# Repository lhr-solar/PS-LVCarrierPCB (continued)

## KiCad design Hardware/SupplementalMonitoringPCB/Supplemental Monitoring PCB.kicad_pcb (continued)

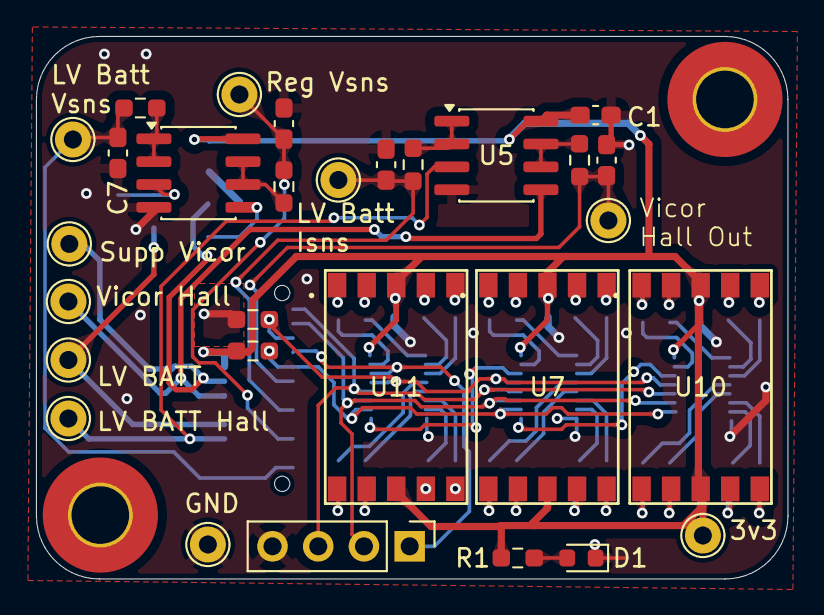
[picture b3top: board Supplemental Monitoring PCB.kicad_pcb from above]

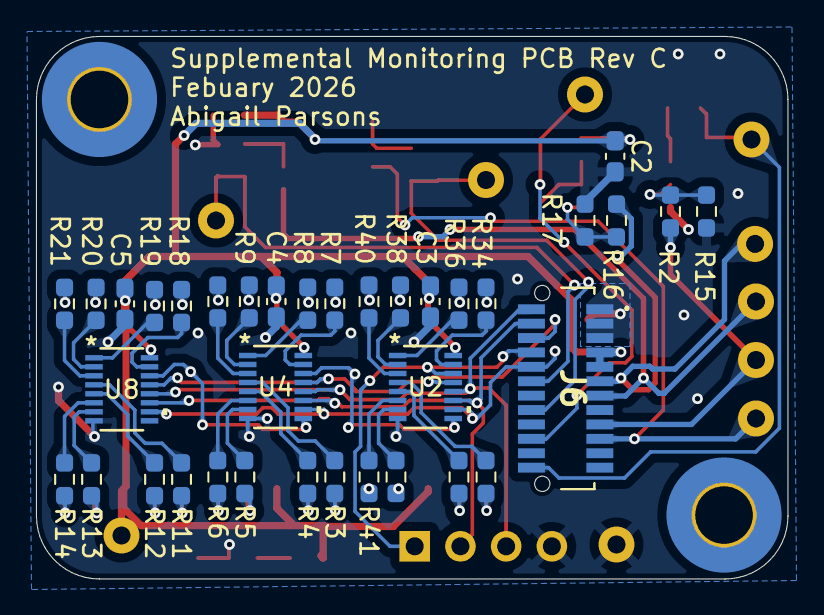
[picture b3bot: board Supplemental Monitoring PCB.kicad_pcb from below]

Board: 2 copper layers, 41.8 x 30.1 mm, 68 parts (36 on the bottom side), 72 nets.

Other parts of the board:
J1: Conn_01x04; PinHeader_1x04_P2.54mm_Vertical

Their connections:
/RCLK: J1.3; also elsewhere on the board
/SER: J1.1; also elsewhere on the board
/SRCLK: J1.2; also elsewhere on the board
GND: J1.4; also elsewhere on the board

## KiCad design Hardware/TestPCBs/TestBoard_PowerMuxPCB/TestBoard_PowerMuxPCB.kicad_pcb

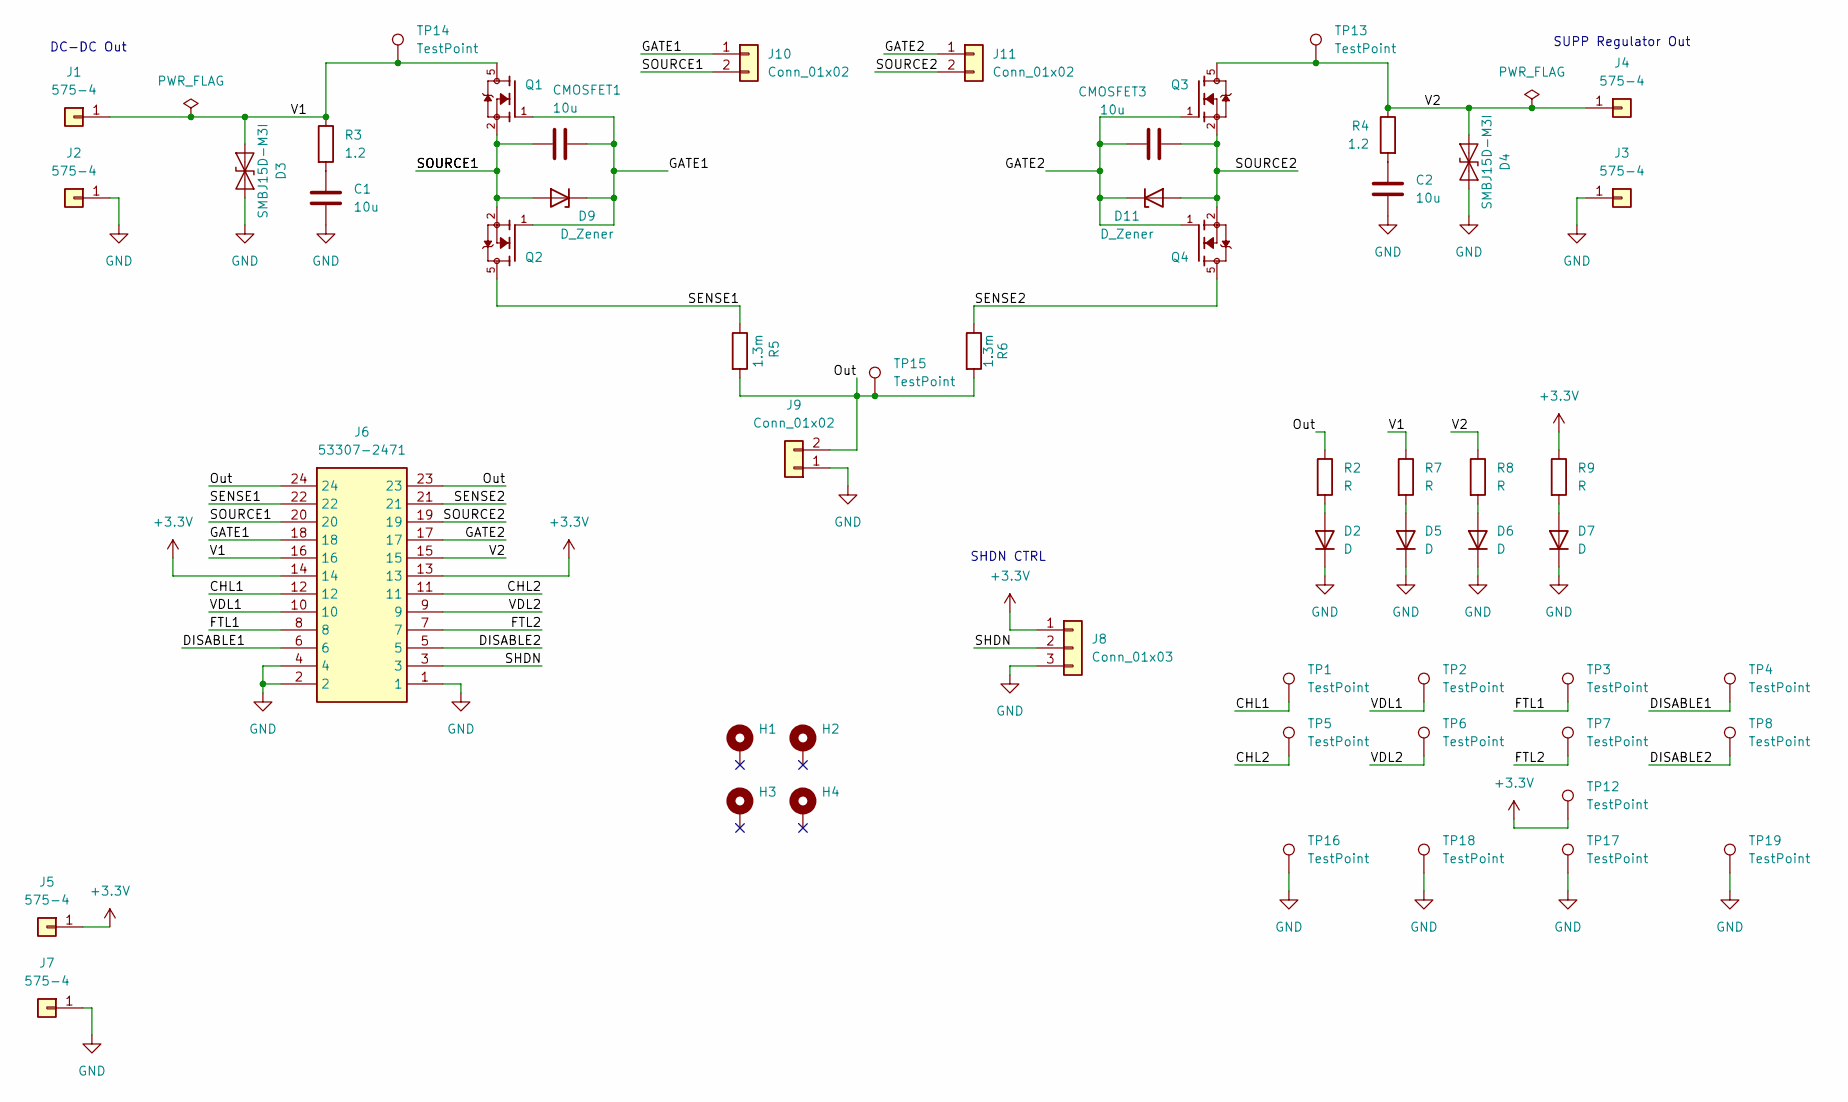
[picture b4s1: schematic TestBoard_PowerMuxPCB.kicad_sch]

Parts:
C1, C2: 10u; C_0805_2012Metric
CMOSFET1, CMOSFET3: 10u; C_0805_2012Metric
D2, D5, D6, D7: D; LED_0603_1608Metric
D3, D4: SMBJ15D-M3I; SMBJ15DM3; MFG PN SMBJ15D-M3I
D9, D11: D_Zener; D_SOD-523; MFG PN DDZ9703T-7
H1, H2, H3, H4: MountingHole_Pad; MountingHole_3.2mm_M3_Pad
J1, J2, J3, J4, J5, J7: 575-4; 5754
J6: 53307-2471; LVMux; Mouser Part Number 538-53307-2471
J8: Conn_01x03; PinHeader_1x03_P2.54mm_Vertical
J9: Conn_01x02; AMASS_XT30UPB-M_1x02_P5.0mm_Vertical
J10, J11: Conn_01x02; PinHeader_1x02_P2.54mm_Vertical
Q1, Q2, Q3, Q4: SQJQ140E-T1_GE3; PARTREV 05-Aug-2019
R2, R7, R8, R9: R; R_0603_1608Metric_Pad0.98x0.95mm_HandSolder
R3, R4: 1.2; R_0805_2012Metric; MFG PN CRCW06031R20FKEA
R5, R6: 1.3m; RESC6432X89N
TP1, TP2, TP3, TP4, TP5, TP6, TP7, TP8, TP12, TP13, TP14, TP15, TP16, TP17, TP18, TP19: TestPoint; TestPoint_Loop_D3.50mm_Drill1.4mm_Beaded

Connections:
+3.3V: J5.1, J6.13, J6.14, J8.1, R9.1, TP12.1
/CHL1: J6.12, TP1.1
/CHL2: J6.11, TP5.1
/DISABLE1: J6.6, TP4.1
/DISABLE2: J6.5, TP8.1
/FTL1: J6.8, TP3.1
/FTL2: J6.7, TP7.1
/GATE1: CMOSFET1.2, D9.1 (K), J6.18, J10.1, Q1.1, Q2.1
/GATE2: CMOSFET3.2, D11.1 (K), J6.17, J11.1, Q3.1, Q4.1
/Out: J6.23, J6.24, J9.2, R2.1, R5.2, R6.2, TP15.1
/SENSE1: J6.22, Q2.5, R5.1
/SENSE2: J6.21, Q4.5, R6.1
/SHDN: J6.3, J8.2
/SOURCE1: CMOSFET1.1, D9.2 (A), J6.20, J10.2, Q1.2, Q1.3, Q1.4, Q2.2, Q2.3, Q2.4
/SOURCE2: CMOSFET3.1, D11.2 (A), J6.19, J11.2, Q3.2, Q3.3, Q3.4, Q4.2, Q4.3, Q4.4
/V1: D3.1 (K), J1.1, J6.16, Q1.5, R3.1, R7.1, TP14.1
/V2: D4.1 (K), J4.1, J6.15, Q3.5, R4.1, R8.1, TP13.1
/VDL1: J6.10, TP2.1
/VDL2: J6.9, TP6.1
GND: C1.2, C2.2, D2.1 (K), D3.2 (A), D4.2 (A), D5.1 (K), D6.1 (K), D7.1 (K), J2.1, J3.1, J6.1, J6.2, J6.4, J7.1, J8.3, J9.1, TP16.1, TP17.1, TP18.1, TP19.1
unnamed: C1.1, R3.2
unnamed: C2.1, R4.2
unnamed: D2.2 (A), R2.2
unnamed: D5.2 (A), R7.2
unnamed: D6.2 (A), R8.2
unnamed: D7.2 (A), R9.2

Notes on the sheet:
SUPP Regulator Out
SHDN CTRL
DC-DC Out

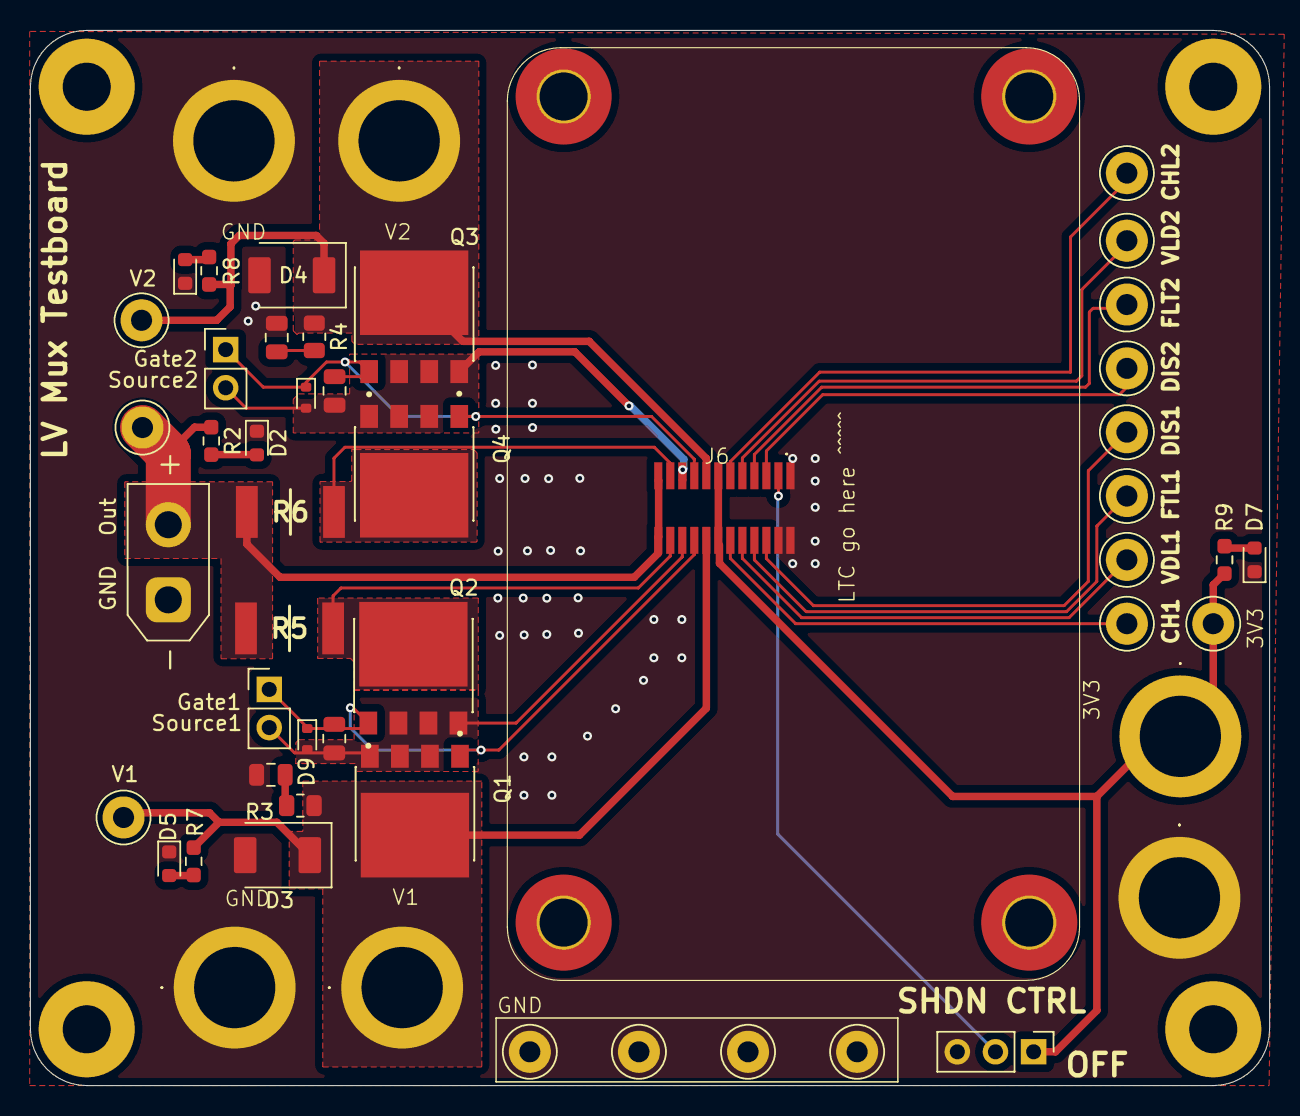
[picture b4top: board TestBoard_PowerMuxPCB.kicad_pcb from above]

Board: 2 copper layers, 82.5 x 70.2 mm, 55 parts (0 on the bottom side), 26 nets.

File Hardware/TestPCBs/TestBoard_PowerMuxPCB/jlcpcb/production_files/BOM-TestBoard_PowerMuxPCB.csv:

Comment,Designator,Footprint,LCSC,Quantity
53307-2471,J6,LVMux,,1
D,D2,LED_0603_1608Metric,,1
R,R8,R_0603_1608Metric_Pad0.98x0.95mm_HandSolder,,1
R,R7,R_0603_1608Metric_Pad0.98x0.95mm_HandSolder,,1
575-4,J5,5754,,1
SQJQ140E-T1_GE3,Q4,SQJQ140E-T1_GE3,,1
D,D5,LED_0603_1608Metric,,1
SQJQ140E-T1_GE3,Q3,SQJQ140E-T1_GE3,,1
1.3m,R5,RESC6432X89N,,1
575-4,J2,5754,,1
SMBJ15D-M3I,D4,SMBJ15DM3,,1
D,D7,LED_0603_1608Metric,,1
575-4,J7,5754,,1
D_Zener,D11,D_SOD-523,,1
SQJQ140E-T1_GE3,Q2,SQJQ140E-T1_GE3,,1
SQJQ140E-T1_GE3,Q1,SQJQ140E-T1_GE3,,1
575-4,J3,5754,,1
D,D6,LED_0603_1608Metric,,1
1.2,R3,R_0805_2012Metric,,1
1.2,R4,R_0805_2012Metric,,1
575-4,J1,5754,,1
575-4,J4,5754,,1
D_Zener,D9,D_SOD-523,,1
R,R2,R_0603_1608Metric_Pad0.98x0.95mm_HandSolder,,1
SMBJ15D-M3I,D3,SMBJ15DM3,,1
10u,C1,C_0805_2012Metric,,1
1.3m,R6,RESC6432X89N,,1
Conn_01x02,J9,AMASS_XT30UPB-M_1x02_P5.0mm_Vertical,,1
R,R9,R_0603_1608Metric_Pad0.98x0.95mm_HandSolder,,1
10u,C2,C_0805_2012Metric,,1
Conn_01x02,J11,PinHeader_1x02_P2.54mm_Vertical,,1
Conn_01x02,J10,PinHeader_1x02_P2.54mm_Vertical,,1

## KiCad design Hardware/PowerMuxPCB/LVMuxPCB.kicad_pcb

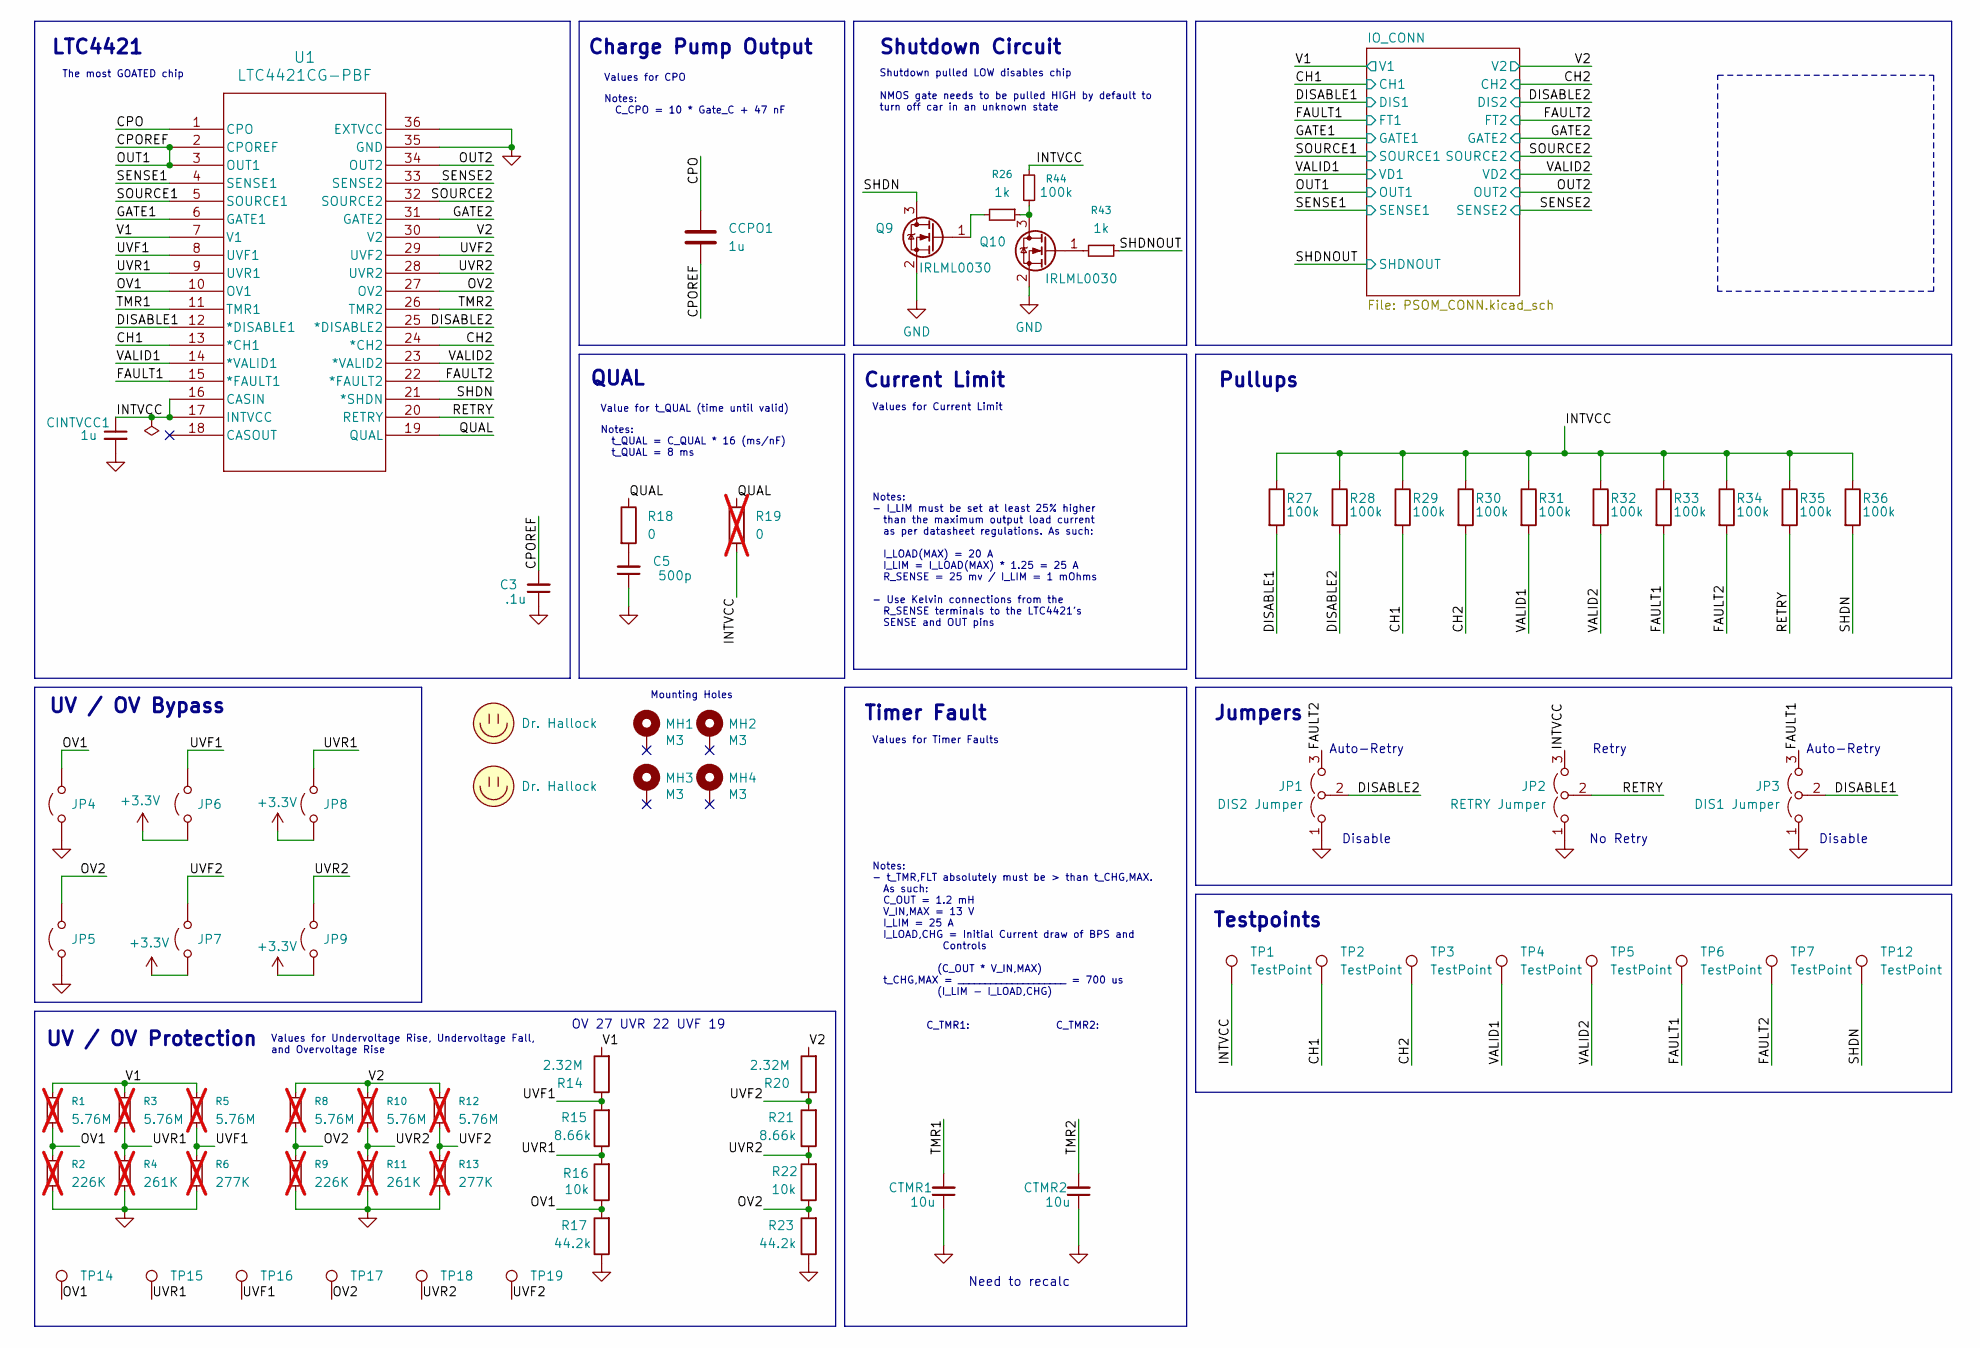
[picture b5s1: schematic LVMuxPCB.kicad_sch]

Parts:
C3: .1u; C_0603_1608Metric
C5: 500p; C_0603_1608Metric
CCPO1: 1u; C_0603_1608Metric
CINTVCC1: 1u; C_0603_1608Metric
CTMR1, CTMR2: 10u; C_0805_2012Metric_Pad1.18x1.45mm_HandSolder
JP1: DIS2 Jumper; PinHeader_1x03_P2.54mm_Vertical
JP2: RETRY Jumper; PinHeader_1x03_P2.54mm_Vertical
JP3: DIS1 Jumper; PinHeader_1x03_P2.54mm_Vertical
JP4, JP5, JP6, JP7, JP8, JP9: Jumper_2_Open; PinHeader_1x02_P2.54mm_Vertical
LOGO1: Dr. Hallock; Hallock_Image_Tiny
LOGO2: Dr. Hallock; LHRs_LOGO
MH1, MH2, MH3, MH4: M3; MountingHole_3.2mm_M3_Pad_TopBottom
Q9, Q10: IRLML0030; SOT-23
R1, R3, R5, R8, R10, R12: 5.76M; R_0603_1608Metric; not fitted
R2, R9: 226K; R_0603_1608Metric; not fitted
R4, R11: 261K; R_0603_1608Metric; not fitted
R6, R13: 277K; R_0603_1608Metric; not fitted
R14, R20: 2.32M; R_0603_1608Metric
R15, R21: 8.66k; R_0603_1608Metric
R16, R22: 10k; R_0603_1608Metric
R17, R23: 44.2k; R_0603_1608Metric
R18: 0; R_0603_1608Metric
R19: 0; R_0603_1608Metric; not fitted
R26, R43: 1k; R_0603_1608Metric
R27, R28, R29, R30, R31, R32, R33, R34, R35, R36, R44: 100k; R_0603_1608Metric
TP1, TP12: TestPoint; TestPoint_Plated_Hole_D2.0mm
TP2, TP3, TP4, TP5, TP6, TP7: TestPoint; TestPoint_Pad_D2.0mm
TP14, TP15, TP16, TP17, TP18, TP19: TestPoint; TestPoint_Pad_D1.0mm
U1: LTC4421CG-PBF

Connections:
+3.3V: JP6.1 (A), JP7.1 (A), JP8.1 (A), JP9.1 (A); also elsewhere on the board
/CH1: R29.2, TP2.1, U1.13 (*CH1); also elsewhere on the board
/CH2: R30.2, TP3.1, U1.24 (*CH2); also elsewhere on the board
/CPO: CCPO1.1, U1.1 (CPO)
/CPOREF: C3.2, CCPO1.2, U1.2 (CPOREF), U1.3 (OUT1); also elsewhere on the board
/DISABLE1: JP3.2 (C), R27.2, U1.12 (*DISABLE1); also elsewhere on the board
/DISABLE2: JP1.2 (C), R28.2, U1.25 (*DISABLE2); also elsewhere on the board
/FAULT1: JP3.3 (B), R33.2, TP6.1, U1.15 (*FAULT1); also elsewhere on the board
/FAULT2: JP1.3 (B), R34.2, TP7.1, U1.22 (*FAULT2); also elsewhere on the board
/GATE1: U1.6 (GATE1); also elsewhere on the board
/GATE2: U1.31 (GATE2); also elsewhere on the board
/INTVCC: CINTVCC1.1, JP2.3 (B), R19.2, R27.1, R28.1, R29.1, R30.1, R31.1, R32.1, R33.1, R34.1, R35.1, R36.1, R44.1, TP1.1, U1.16 (CASIN), U1.17 (INTVCC); also elsewhere on the board
/OUT2: U1.34 (OUT2); also elsewhere on the board
/OV1: JP4.2 (B), R1.2, R2.1, R16.1, R17.2, TP14.1, U1.10 (OV1)
/OV2: JP5.2 (B), R8.2, R9.1, R22.1, R23.2, TP17.1, U1.27 (OV2)
/QUAL: R18.1, R19.1, U1.19 (QUAL)
/RETRY: JP2.2 (C), R35.2, U1.20 (RETRY)
/SENSE1: U1.4 (SENSE1); also elsewhere on the board
/SENSE2: U1.33 (SENSE2); also elsewhere on the board
/SHDN: Q9.3 (D), R36.2, TP12.1, U1.21 (*SHDN)
/SHDNOUT: R43.1; also elsewhere on the board
/SOURCE1: U1.5 (SOURCE1); also elsewhere on the board
/SOURCE2: U1.32 (SOURCE2); also elsewhere on the board
/TMR1: CTMR1.2, U1.11 (TMR1)
/TMR2: CTMR2.2, U1.26 (TMR2)
/UVF1: JP6.2 (B), R5.2, R6.1, R14.1, R15.2, TP16.1, U1.8 (UVF1)
/UVF2: JP7.2 (B), R12.2, R13.1, R20.1, R21.2, TP19.1, U1.29 (UVF2)
/UVR1: JP8.2 (B), R3.2, R4.1, R15.1, R16.2, TP15.1, U1.9 (UVR1)
/UVR2: JP9.2 (B), R10.2, R11.1, R21.1, R22.2, TP18.1, U1.28 (UVR2)
/V1: R1.1, R3.1, R5.1, R14.2, U1.7 (V1); also elsewhere on the board
/V2: R8.1, R10.1, R12.1, R20.2, U1.30 (V2); also elsewhere on the board
/VALID1: R31.2, TP4.1, U1.14 (*VALID1); also elsewhere on the board
/VALID2: R32.2, TP5.1, U1.23 (*VALID2); also elsewhere on the board
GND: C3.1, C5.1, CINTVCC1.2, CTMR1.1, CTMR2.1, JP1.1 (A), JP2.1 (A), JP3.1 (A), JP4.1 (A), JP5.1 (A), Q9.2 (S), Q10.2 (S), R2.2, R4.2, R6.2, R9.2, R11.2, R13.2, R17.1, R23.1, U1.35 (GND), U1.36 (EXTVCC); also elsewhere on the board
unnamed: C5.2, R18.2
unnamed: Q9.1 (G), R26.2
unnamed: Q10.3 (D), R26.1, R44.2
unnamed: Q10.1 (G), R43.2

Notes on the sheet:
Shutdown Circuit
LTC4421
Value for t_QUAL (time until valid)
UV / OV Protection
Jumpers
QUAL
Disable
Charge Pump Output
Retry
Values for Undervoltage Rise, Undervoltage Fall, and Overvoltage Rise
The most GOATED chip
Notes: - t_TMR,FLT absolutely must be > than t_CHG,MAX. As such: C_OUT = 1.2 mH V_IN,MAX = 13 V I_LIM = 25 A I_LOAD,CHG = Initial Current draw of BPS and Controls (C_OUT * V_IN,MAX) t_CHG,MAX = ____________________ = 700 us (I_LIM - I_LOAD,CHG)
C_TMR1: C_TMR2:
Values for CPO
Notes: C_CPO = 10 * Gate_C + 47 nF
Need to recalc
Notes: t_QUAL = C_QUAL * 16 (ms/nF) t_QUAL = 8 ms
Notes: - I_LIM must be set at least 25% higher than the maximum output load current as per datasheet regulations. As such: I_LOAD(MAX) = 20 A I_LIM = I_LOAD(MAX) * 1.25 = 25 A R_SENSE = 25 mv / I_LIM = 1 mOhms - Use Kelvin connections from the R_SENSE terminals to the LTC4421's SENSE and OUT pins
Current Limit
UV / OV Bypass
Values for Timer Faults
Values for Current Limit
Pullups
Shutdown pulled LOW disables chip NMOS gate needs to be pulled HIGH by default to turn off car in an unknown state
Mounting Holes
OV 27 UVR 22 UVF 19
Auto-Retry
No Retry
Testpoints
Timer Fault

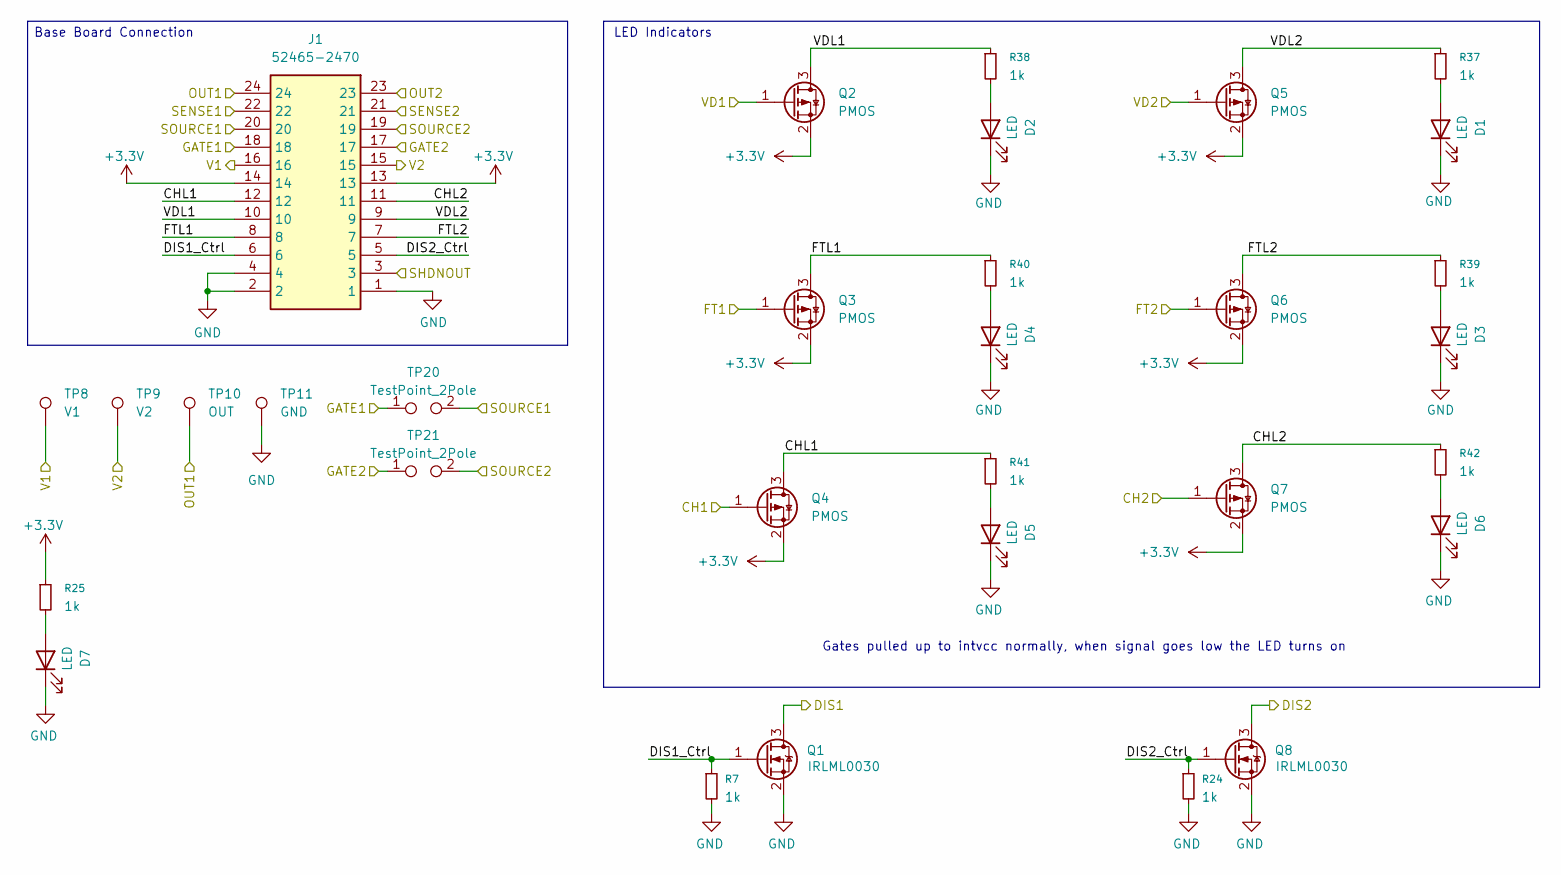
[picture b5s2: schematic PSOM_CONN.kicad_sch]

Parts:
D1, D2, D3, D4, D5, D6, D7: LED; LED_0603_1608Metric
J1: 52465-2470; 524652470
Q1, Q8: IRLML0030; SOT-23
Q2, Q3, Q4, Q5, Q6, Q7: PMOS; IRLML5203TRPBF; LCSC P/N C2592
R7, R24, R25, R37, R38, R39, R40, R41, R42: 1k; R_0603_1608Metric
TP8: V1; TestPoint_Plated_Hole_D2.0mm
TP9: V2; TestPoint_Plated_Hole_D2.0mm
TP10: OUT; TestPoint_Plated_Hole_D2.0mm
TP11: GND; TestPoint_Plated_Hole_D2.0mm
TP20, TP21: TestPoint_2Pole; TestPoint_2Pads_Pitch2.54mm_Drill0.8mm

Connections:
+3.3V: J1.13, J1.14, Q2.2 (S), Q3.2 (S), Q4.2 (S), Q5.2 (S), Q6.2 (S), Q7.2 (S), R25.1; also elsewhere on the board
/CH1: Q4.1 (G); also elsewhere on the board
/CH2: Q7.1 (G); also elsewhere on the board
/CPOREF: J1.24, TP10.1; also elsewhere on the board
/DISABLE1: Q1.3 (D); also elsewhere on the board
/DISABLE2: Q8.3 (D); also elsewhere on the board
/FAULT1: Q3.1 (G); also elsewhere on the board
/FAULT2: Q6.1 (G); also elsewhere on the board
/GATE1: J1.18, TP20.1; also elsewhere on the board
/GATE2: J1.17, TP21.1; also elsewhere on the board
/IO_CONN/CHL1: J1.12, Q4.3 (D), R41.1
/IO_CONN/CHL2: J1.11, Q7.3 (D), R42.1
/IO_CONN/DIS1_Ctrl: J1.6, Q1.1 (G), R7.1
/IO_CONN/DIS2_Ctrl: J1.5, Q8.1 (G), R24.1
/IO_CONN/FTL1: J1.8, Q3.3 (D), R40.1
/IO_CONN/FTL2: J1.7, Q6.3 (D), R39.1
/IO_CONN/VDL1: J1.10, Q2.3 (D), R38.1
/IO_CONN/VDL2: J1.9, Q5.3 (D), R37.1
/OUT2: J1.23; also elsewhere on the board
/SENSE1: J1.22; also elsewhere on the board
/SENSE2: J1.21; also elsewhere on the board
/SHDNOUT: J1.3; also elsewhere on the board
/SOURCE1: J1.20, TP20.2; also elsewhere on the board
/SOURCE2: J1.19, TP21.2; also elsewhere on the board
/V1: J1.16, TP8.1; also elsewhere on the board
/V2: J1.15, TP9.1; also elsewhere on the board
/VALID1: Q2.1 (G); also elsewhere on the board
/VALID2: Q5.1 (G); also elsewhere on the board
GND: D1.1 (K), D2.1 (K), D3.1 (K), D4.1 (K), D5.1 (K), D6.1 (K), D7.1 (K), J1.1, J1.2, J1.4, Q1.2 (S), Q8.2 (S), R7.2, R24.2, TP11.1; also elsewhere on the board
unnamed: D1.2 (A), R37.2
unnamed: D2.2 (A), R38.2
unnamed: D3.2 (A), R39.2
unnamed: D4.2 (A), R40.2
unnamed: D5.2 (A), R41.2
unnamed: D6.2 (A), R42.2
unnamed: D7.2 (A), R25.2

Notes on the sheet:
Base Board Connection
LED Indicators
Gates pulled up to intvcc normally, when signal goes low the LED turns on

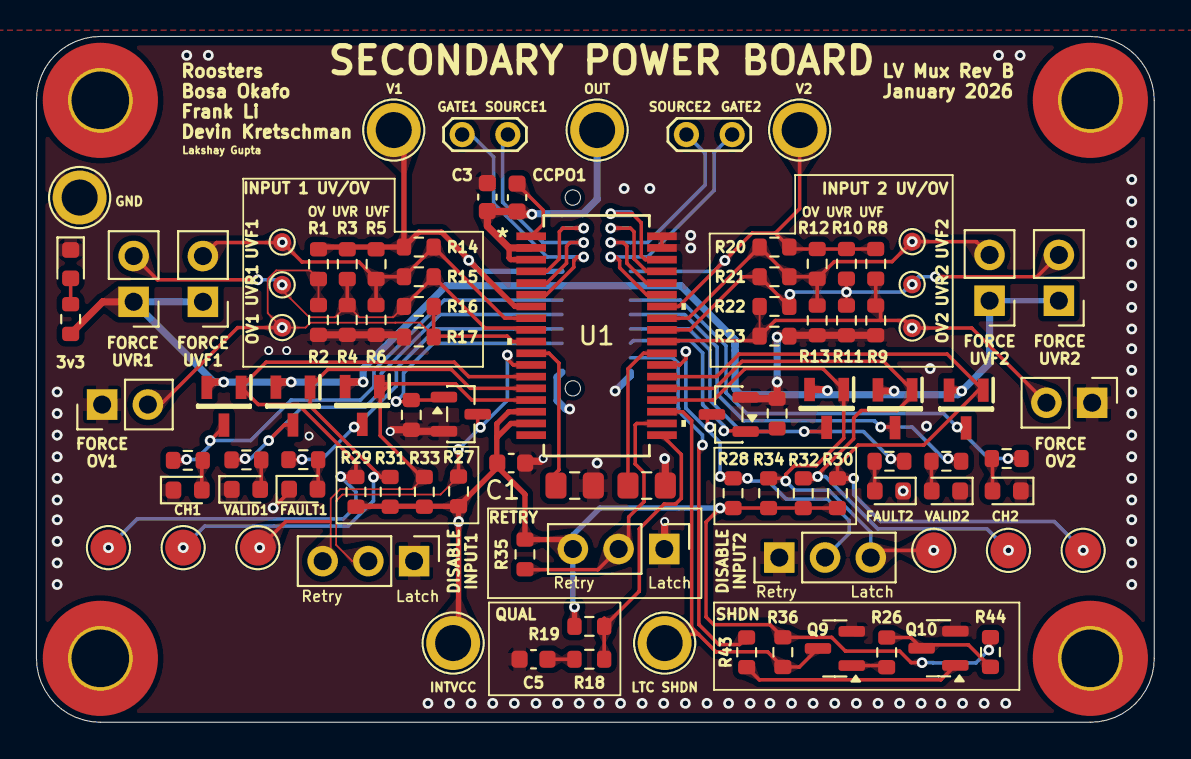
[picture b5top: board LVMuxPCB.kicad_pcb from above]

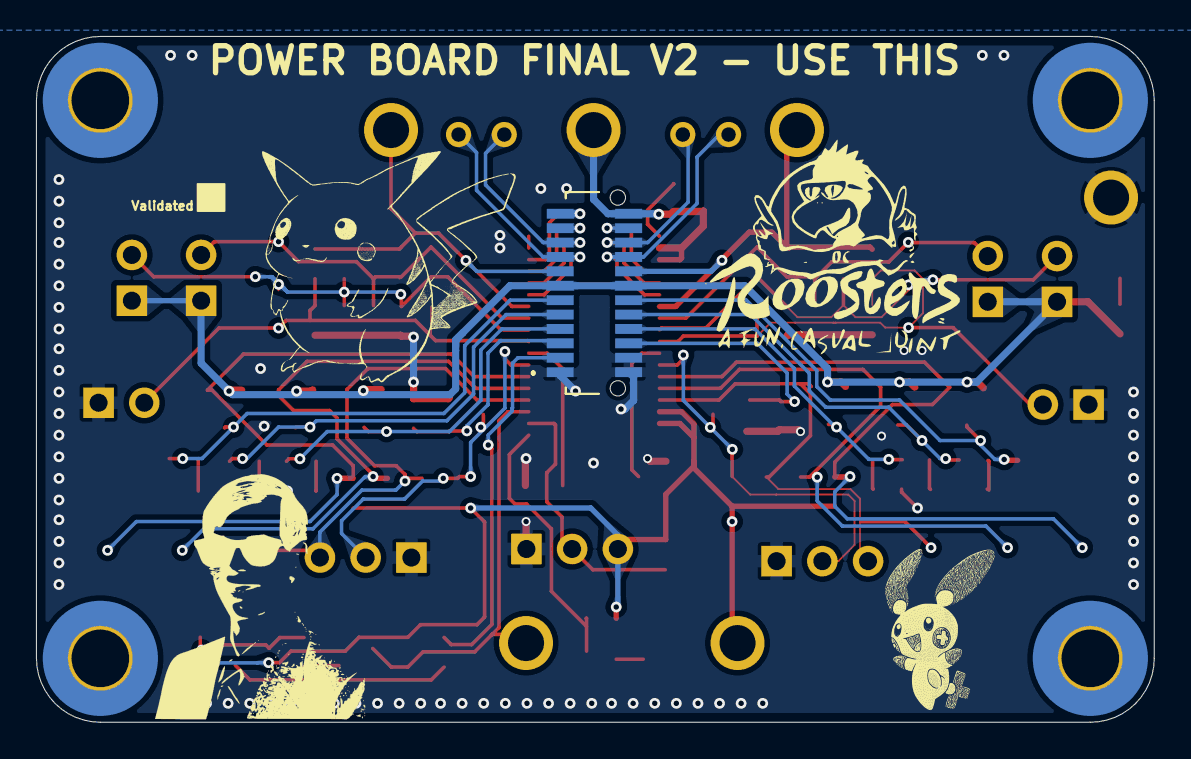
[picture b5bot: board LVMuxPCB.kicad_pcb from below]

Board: 2 copper layers, 62.1 x 38.1 mm, 104 parts (2 on the bottom side), 53 nets.

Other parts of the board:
C1: 1u; C_0603_1608Metric

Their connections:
/INTVCC: C1.1; also elsewhere on the board
GND: C1.2; also elsewhere on the board

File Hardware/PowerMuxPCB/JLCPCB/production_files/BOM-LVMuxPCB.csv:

Comment,Designator,Footprint,LCSC,Quantity
.1u,C3,C_0603_1608Metric,C14663,1
0,R18,R_0603_1608Metric,C21189,1
100k,"R27,R28,R29,R30,R31,R32,R33,R34,R35,R36,R44",R_0603_1608Metric,C25803,11
10k,"R16,R22",R_0603_1608Metric,C25804,2
10u,"CTMR1,CTMR2",C_0805_2012Metric_Pad1.18x1.45mm_HandSolder,C440198,2
1k,"R24,R25,R26,R37,R38,R39,R40,R41,R42,R43,R7",R_0603_1608Metric,C21190,11
1u,"C1,CCPO1",C_0603_1608Metric,C15849,2
2.32M,"R14,R20",R_0603_1608Metric,C482791,2
44.2k,"R17,R23",R_0603_1608Metric,C23056,2
500p,C5,C_0603_1608Metric,C3879676,1
8.66k,"R15,R21",R_0603_1608Metric,C103851,2
IRLML0030,"Q1,Q10,Q8,Q9",SOT-23,C67272,4
LED,"D1,D2,D3,D4,D5,D6,D7",LED_0603_1608Metric,C7371904,7
PMOS,"Q2,Q3,Q4,Q5,Q6,Q7",IRLML5203TRPBF,C2592,6
261K,,R_0603_1608Metric,,0
5.76M,,R_0603_1608Metric,,0
277K,,R_0603_1608Metric,,0
5.76M,,R_0603_1608Metric,,0
TestPoint,TP14,TestPoint_Pad_D1.0mm,,1
LTC4421CG-PBF,U1,LTC4421CG-PBF,,1
TestPoint,TP15,TestPoint_Pad_D1.0mm,,1
TestPoint,TP17,TestPoint_Pad_D1.0mm,,1
5.76M,,R_0603_1608Metric,,0
TestPoint,TP19,TestPoint_Pad_D1.0mm,,1
TestPoint,TP18,TestPoint_Pad_D1.0mm,,1
261K,,R_0603_1608Metric,,0
226K,,R_0603_1608Metric,,0
277K,,R_0603_1608Metric,,0
5.76M,,R_0603_1608Metric,,0
5.76M,,R_0603_1608Metric,,0
TestPoint,TP16,TestPoint_Pad_D1.0mm,,1
226K,,R_0603_1608Metric,,0
5.76M,,R_0603_1608Metric,,0
52465-2470,J1,524652470,,1

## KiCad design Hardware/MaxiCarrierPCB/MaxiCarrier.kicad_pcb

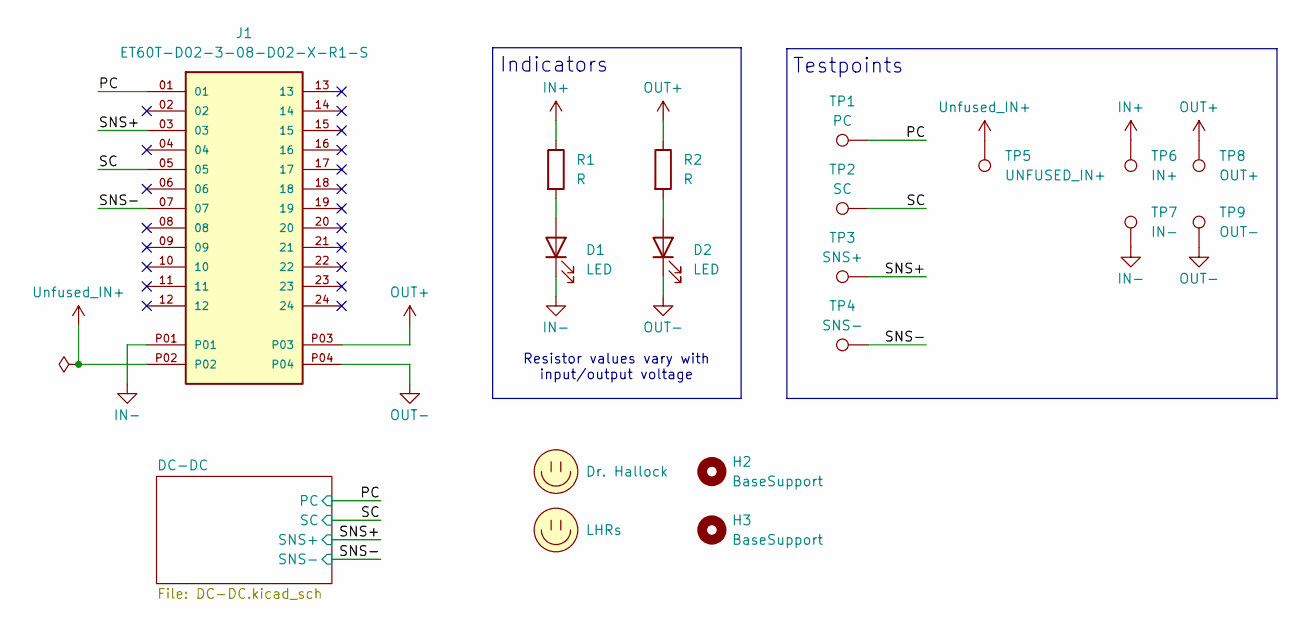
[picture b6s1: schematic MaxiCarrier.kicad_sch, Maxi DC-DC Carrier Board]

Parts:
D1, D2: LED; LED_0603_1608Metric_Pad1.05x0.95mm_HandSolder
H2, H3: BaseSupport; MountingHole_3.2mm_M3
J1: ET60T-D02-3-08-D02-X-R1-S; SAMTEC_ET60T-D02-3-08-D02-X-R1-S; PARTREV J
LOGO1: Dr. Hallock; Hallock_Image
LOGO2: LHRs; LHRs_LOGO
R1, R2: R; R_1206_3216Metric
TP1: PC; TestPoint_Pad_1.0x1.0mm
TP2: SC; TestPoint_Pad_1.0x1.0mm
TP3: SNS+; TestPoint_Pad_1.0x1.0mm
TP4: SNS-; TestPoint_Pad_1.0x1.0mm
TP5: UNFUSED_IN+; TestPoint_Pad_1.0x1.0mm
TP6: IN+; TestPoint_Pad_1.0x1.0mm
TP7: IN-; TestPoint_Pad_1.0x1.0mm
TP8: OUT+; TestPoint_Pad_1.0x1.0mm
TP9: OUT-; TestPoint_Pad_1.0x1.0mm

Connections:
/PC: J1.01, TP1.1; also elsewhere on the board
/SC: J1.05, TP2.1; also elsewhere on the board
/SNS+: J1.03, TP3.1; also elsewhere on the board
/SNS-: J1.07, TP4.1; also elsewhere on the board
IN+: R1.1, TP6.1; also elsewhere on the board
IN-: D1.1 (K), J1.P01, TP7.1; also elsewhere on the board
unnamed: D1.2 (A), R1.2
unnamed: D2.2 (A), R2.2
OUT+: J1.P03, R2.1, TP8.1; also elsewhere on the board
OUT-: D2.1 (K), J1.P04, TP9.1; also elsewhere on the board
Unfused_IN+: J1.P02, TP5.1; also elsewhere on the board

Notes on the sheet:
Testpoints
Indicators
Resistor values vary with input/output voltage

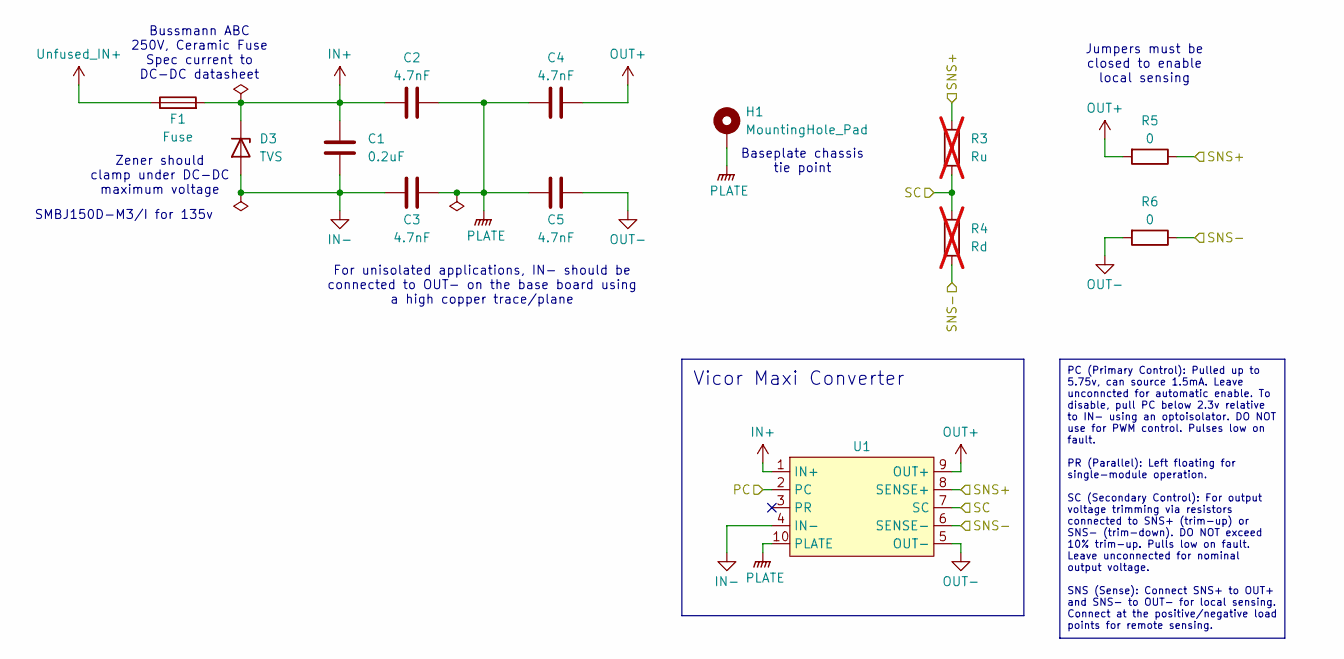
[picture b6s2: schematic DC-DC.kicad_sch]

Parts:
C1: 0.2uF; C_1812_4532Metric_Pad1.57x3.40mm_HandSolder
C2, C3, C4, C5: 4.7nF; C_1812_4532Metric_Pad1.57x3.40mm_HandSolder
D3: TVS; D_SMB_Handsoldering
F1: Fuse; Fuseholder_Clip-6.3x32mm_Littelfuse_122_Inline_P34.21x7.62m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
H1: MountingHole_Pad; MountingHole_3.2mm_M3_Pad_TopBottom
R3: Ru; R_0603_1608Metric_Pad0.98x0.95mm_HandSolder; not fitted
R4: Rd; R_0603_1608Metric_Pad0.98x0.95mm_HandSolder; not fitted
R5, R6: 0; R_0603_1608Metric_Pad0.98x0.95mm_HandSolder
U1: Vicor_Maxi_Brick

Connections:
/PC: U1.2 (PC); also elsewhere on the board
/SC: R3.1, R4.1, U1.7 (SC); also elsewhere on the board
/SNS+: R3.2, R5.1, U1.8 (SENSE+); also elsewhere on the board
/SNS-: R4.2, R6.1, U1.6 (SENSE-); also elsewhere on the board
IN+: C1.1, C2.1, D3.1 (K), F1.2, U1.1 (IN+); also elsewhere on the board
IN-: C1.2, C3.1, D3.2 (A), U1.4 (IN-); also elsewhere on the board
OUT+: C4.2, R5.2, U1.9 (OUT+); also elsewhere on the board
OUT-: C5.2, R6.2, U1.5 (OUT-); also elsewhere on the board
PLATE: C2.2, C3.2, C4.1, C5.1, H1.1, U1.10 (PLATE)
Unfused_IN+: F1.1; also elsewhere on the board

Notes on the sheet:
Baseplate chassis tie point
Bussmann ABC 250V, Ceramic Fuse Spec current to DC-DC datasheet
Zener should clamp under DC-DC maximum voltage
SMBJ150D-M3/I for 135v
For unisolated applications, IN- should be connected to OUT- on the base board using a high copper trace/plane
Jumpers must be closed to enable local sensing
Vicor Maxi Converter
PC (Primary Control): Pulled up to 5.75v, can source 1.5mA. Leave unconncted for automatic enable. To disable, pull PC below 2.3v relative to IN- using an optoisolator. DO NOT use for PWM control. Pulses low on fault. PR (Parallel): Left floating for single-module operation. SC (Secondary Control):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
